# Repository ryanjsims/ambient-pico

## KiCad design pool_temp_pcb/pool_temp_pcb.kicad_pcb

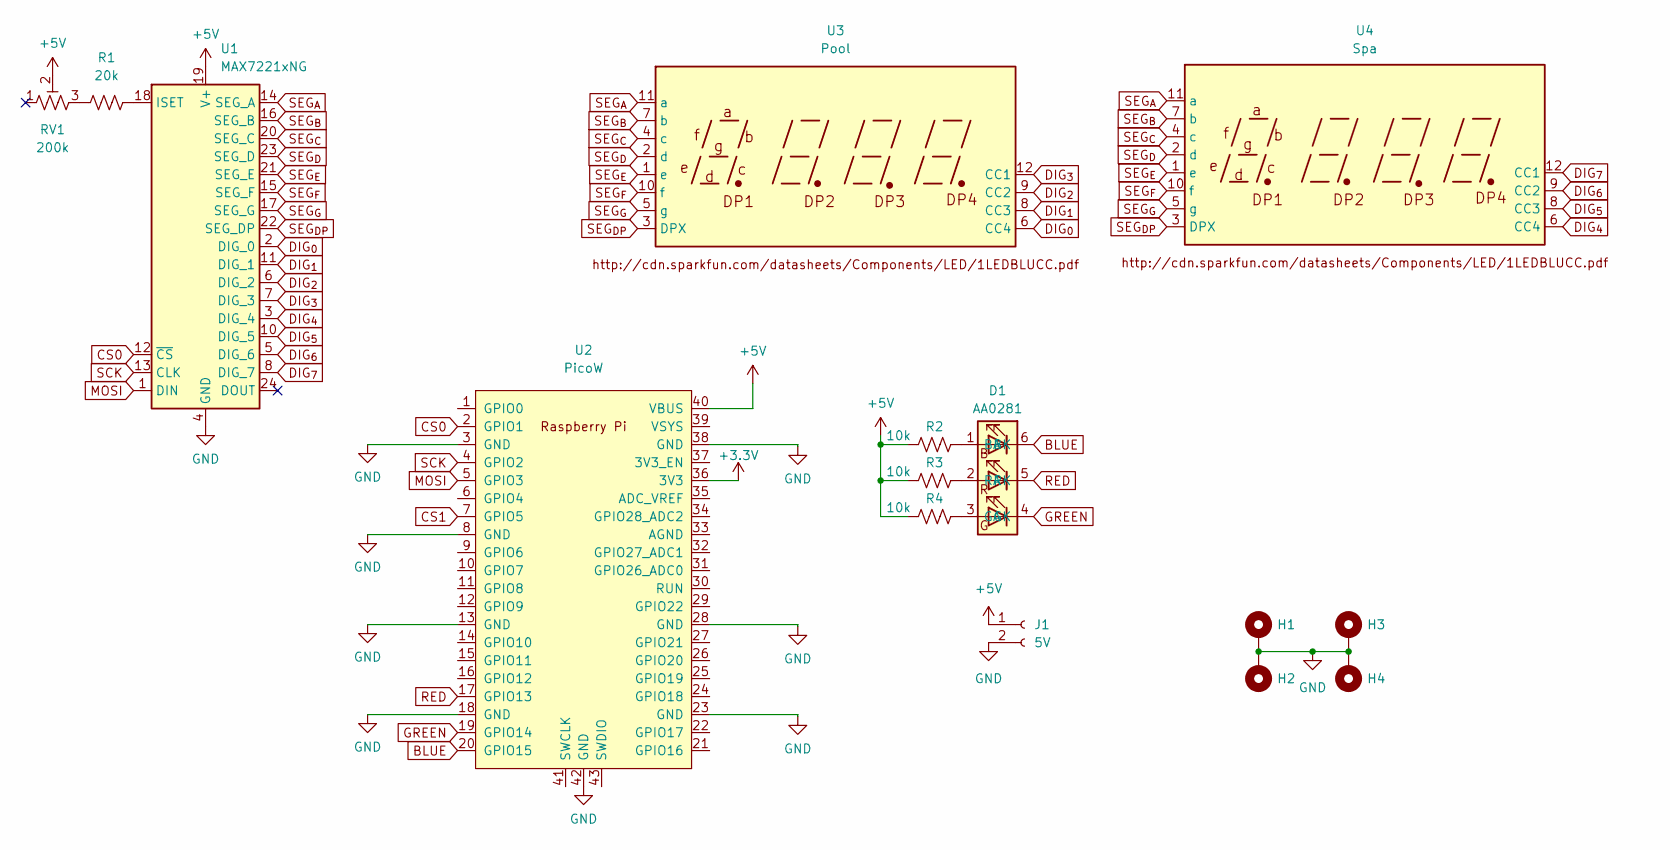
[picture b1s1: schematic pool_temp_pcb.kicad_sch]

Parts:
D1: AA0281; LED_RGB_5050-6
H1: Hole; MountingHole_3.2mm_M3_Pad_TopBottom
H2, H3, H4: MountingHole_Pad; MountingHole_3.2mm_M3_Pad_TopBottom
J1: 5V; PinHeader_1x02_P2.54mm_Vertical
R1: 20k; R_Axial_DIN0411_L9.9mm_D3.6mm_P15.24mm_Horizontal
R2, R3, R4: 10k; R_Axial_DIN0411_L9.9mm_D3.6mm_P15.24mm_Horizontal
RV1: 200k; Potentiometer_Runtron_RM-065_Vertical
U1: MAX7221xNG; DIP-24_W7.62mm
U2: PicoW; RPi_PicoW_SMD_TH
U3: Pool; ATA8041AB
U4: Spa; ATA8041AB

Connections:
+3.3V: U2.36 (3V3)
+5V: J1.1, R2.1, R3.1, R4.1, RV1.2, U1.19 (V+), U2.40 (VBUS)
BLUE: D1.6 (BK), U2.20 (GPIO15)
CS0: U1.12 (~CS), U2.2 (GPIO1)
CS1: U2.7 (GPIO5)
DIG_{0}: U1.2 (DIG_0), U3.6 (CC4)
DIG_{1}: U1.11 (DIG_1), U3.8 (CC3)
DIG_{2}: U1.6 (DIG_2), U3.9 (CC2)
DIG_{3}: U1.7 (DIG_3), U3.12 (CC1)
DIG_{4}: U1.3 (DIG_4), U4.6 (CC4)
DIG_{5}: U1.10 (DIG_5), U4.8 (CC3)
DIG_{6}: U1.5 (DIG_6), U4.9 (CC2)
DIG_{7}: U1.8 (DIG_7), U4.12 (CC1)
GND: H1.1, H2.1, H3.1, H4.1, J1.2, U1.4 (GND), U1.9 (GND), U2.3 (GND), U2.8 (GND), U2.13 (GND), U2.18 (GND), U2.23 (GND), U2.28 (GND), U2.38 (GND), U2.42 (GND)
GREEN: D1.4 (GK), U2.19 (GPIO14)
MOSI: U1.1 (DIN), U2.5 (GPIO3)
unnamed: D1.1 (BA), R2.2
unnamed: D1.2 (RA), R3.2
unnamed: D1.3 (GA), R4.2
unnamed: R1.1, RV1.3
unnamed: R1.2, U1.18 (ISET)
RED: D1.5 (RK), U2.17 (GPIO13)
SCK: U1.13 (CLK), U2.4 (GPIO2)
SEG_{A}: U1.14 (SEG_A), U3.11 (a), U4.11 (a)
SEG_{B}: U1.16 (SEG_B), U3.7 (b), U4.7 (b)
SEG_{C}: U1.20 (SEG_C), U3.4 (c), U4.4 (c)
SEG_{DP}: U1.22 (SEG_DP), U3.3 (DPX), U4.3 (DPX)
SEG_{D}: U1.23 (SEG_D), U3.2 (d), U4.2 (d)
SEG_{E}: U1.21 (SEG_E), U3.1 (e), U4.1 (e)
SEG_{F}: U1.15 (SEG_F), U3.10 (f), U4.10 (f)
SEG_{G}: U1.17 (SEG_G), U3.5 (g), U4.5 (g)

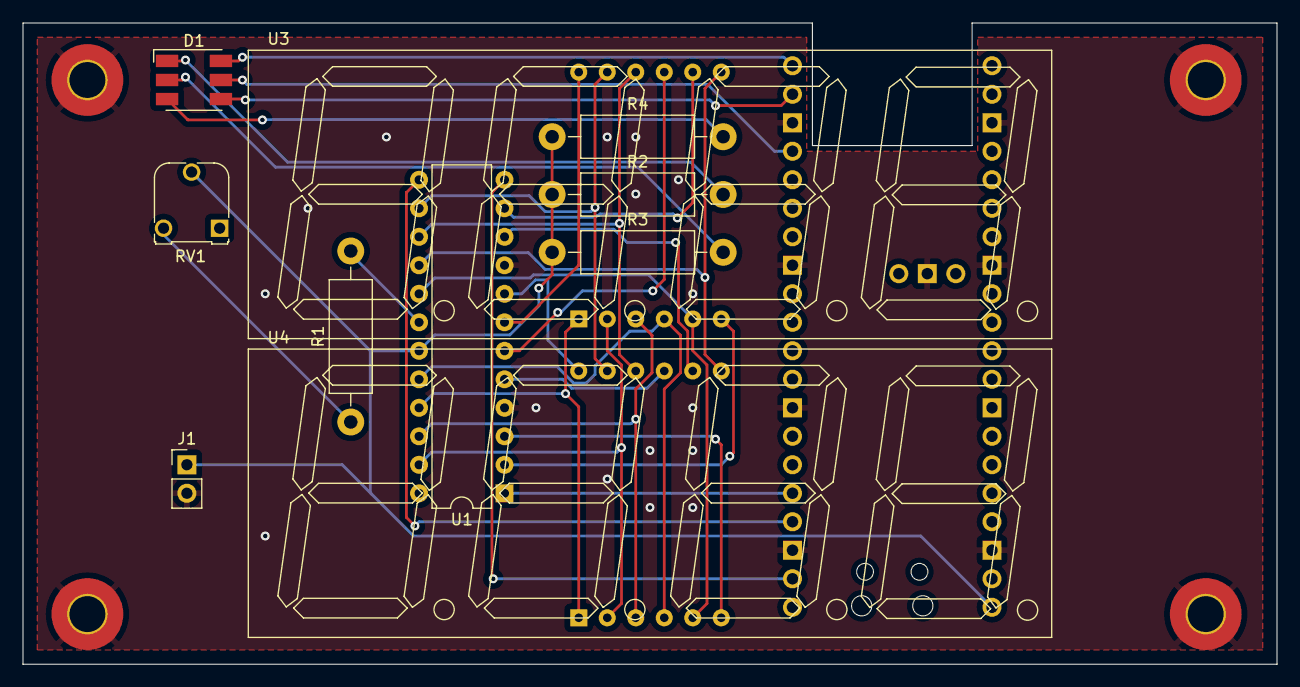
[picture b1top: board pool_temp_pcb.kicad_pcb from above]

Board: 2 copper layers, 111.8 x 57.1 mm, 15 parts (1 on the bottom side), 29 nets.

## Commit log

2023-01-06 Got a simple tcp_client put together
2023-01-06 Add tcp_server.py test script
2023-01-06 Add basic logging defines
2023-01-08 Add tcp_tls_client, move tcp_client out of line, add http(s)_client, update pico-sdk commit
2023-01-08 Add keys using cmake environment variables
2023-01-10 Add circular buffer iterator
2023-01-10 Add websocket headers to https client
2023-01-10 Remove reference from read
2023-01-10 Add websocket client
2023-01-10 Add PoC websocket connection
2023-01-10 Add eio_client
2023-01-11 Add nlohmann json as submodule
2023-01-11 Added socket.io client, not actually in use yet
2023-01-11 Got sio_client generally working
2023-01-12 Reduced the number of copies of packets made.
2023-01-17 Added several features in the name of reliability
2023-01-24 Add function to enable watchdog refreshing
2023-01-24 Add ms since boot to log messages
2023-01-24 Add ensure init function to double check the chip is enabled
2023-01-24 Reliability upgrades
2023-01-27 Add second display
2023-01-27 Add kicad files
2023-01-27 Update gitignore, add 7 segment pinout
2023-01-28 Fix failed reconnects
2023-01-28 Update schematic
2023-01-28 Add pcb ignore files
2023-01-30 Minor tweaks
2023-02-05 Add pico-examples as submodule
2023-02-05 Add rgb_matrix control code and usage example
2023-02-05 Update pico-sdk to include pico/rand.h lib
2023-02-05 Remove hub75 example from build targets
2023-02-05 Bump examples commit
2023-02-05 Experiment with using an array rather than a map for the trails
2023-02-06 Add behavior rules
2023-02-06 Add trim pot
2023-02-07 Update pico-sdk commit
2023-02-07 Layout version 1 of temperature pcb
2023-02-11 Optimize slime mold cellular automata
2023-02-11 Pull latest pico-sdk
